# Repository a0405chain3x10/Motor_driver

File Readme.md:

# Discrete H-Bridge DC Motor Driver

This repository contains the KiCad schematics and PCB layout files for a custom DC motor driver. Designed around a discrete MOSFET H-Bridge topology, the board incorporates dedicated gate drivers and a hardware-level logic safety interlock to prevent catastrophic shoot-through conditions.

## Hardware Architecture
The motor driver is built to handle high-current DC loads using a robust discrete component approach:
*   **Power Delivery:** The main power stage accepts a 12V input via a dedicated screw terminal (J1), supported by a 220uF/25V electrolytic bulk capacitor (C7) to handle transient loads.
*   **Logic Power:** A separate 3.3V input (J3) is utilized to power the onboard logic gates and safely interface with low-voltage microcontrollers.
*   **H-Bridge Configuration:** The switching stage utilizes two PMOS (Q1, Q3) and two NMOS (Q2, Q4) transistors in a standard H-Bridge layout to control motor direction and speed.
*   **Gate Driving:** Two TC4428xOA ICs (U1, U2) are used to provide the necessary current to rapidly charge and discharge the MOSFET gates, ensuring highly efficient PWM switching and minimizing thermal dissipation.
*   **Motor Output:** The driven motor connects directly to the H-Bridge via a 2-pin screw terminal (J4) labeled `M+` and `M-`.

## Hardware Safety Interlock
To protect the H-Bridge from short circuits caused by simultaneous directional commands (shoot-through), the board features a physical logic-gate safety layer:
*   **Logic ICs:** The interlock circuit is constructed using standard DIP-packaged 74HC08 (AND) and 74HC04 (NOT/Inverter) logic chips.
*   **Signal Processing:** Raw `R` and `L` input signals from the control connector (J2) are processed through the logic gates to generate mutually exclusive `R_Safe` and `L_Safe` signals. 
*   **Fail-Safe Operation:** If both directional inputs are triggered simultaneously (either by software bug or electrical noise), the hardware logic overrides the input and prevents the active signals from reaching the TC4428xOA gate drivers, keeping the MOSFETs safely deactivated.

## PCB Layout & Design Features
The physical dual-layer board is optimized for current handling and thermal management:
*   **High-Current Routing:** The `M+` and `M-` motor output paths utilize exceptionally thick copper traces routed across both the top and bottom layers to handle heavy current loads without overheating.
*   **Thermal Management:** The four TO-220 MOSFETs (Q1-Q4) are aligned sequentially along the edge of the board, allowing them to share a single, continuous heatsink for optimal thermal dissipation.
*   **Mixed-Technology Assembly:** The design smartly combines through-hole components for robust mechanical connections (connectors, bulk capacitors, DIP logic ICs) with surface-mount (SMD) components for the gate drivers, decoupling capacitors, and pull-down resistors to save board space and optimize routing.

## Bill of Materials (BOM)

### Semiconductors & ICs
| Reference | Part | Package | Description | Quantity |
| :--- | :--- | :--- | :--- | :--- |
| U1, U2 | TC4428xOA | SOIC-8 (SMD) | 1.5A Dual High-Speed Gate Driver | 2 |
| Q1, Q3 | PMOS Transistor | TO-220 | High-Side P-Channel Power MOSFET | 2 |
| Q2, Q4 | NMOS Transistor | TO-220 | Low-Side N-Channel Power MOSFET | 2 |
| U5, U6 | 74HC08 | DIP-14 | Quad 2-Input AND Gate | 2 |
| U3, U4 | 74HC04 | DIP-14 | Hex Inverter (NOT Gate) | 2 |

### Passives (Resistors & Capacitors)
| Reference | Value | Package | Description | Quantity |
| :--- | :--- | :--- | :--- | :--- |
| C7 | 220uF / 25V | Radial (THT) | Bulk Electrolytic Decoupling Capacitor | 1 |
| C4, C6, C8 | 1uF / 25V | SMD | Ceramic Decoupling Capacitor | 3 |
| C3, C5, C9, C10, C11, C12, C13 | 100nF (0.1uF) | SMD | Ceramic Decoupling Capacitor | 7 |
| R1, R2, R3, R4 | 10 Ω | SMD | Gate Current Limiting Resistor | 4 |
| R5, R6, R7, R8 | 10k Ω | SMD | Input Signal Pull-down Resistor | 4 |
| R9, R10, R11, R12 | 47k Ω | SMD | Gate Pull-down Resistor | 4 |

### Connectors & Hardware
| Reference | Part | Description | Quantity |
| :--- | :--- | :--- | :--- |
| J1 | 2-Pin Screw Terminal | 12V Main Power Input | 1 |
| J4 | 2-Pin Screw Terminal | Motor Output (M+, M-) | 1 |
| J2 | 3-Pin Header/Terminal | Logic Inputs (R, L, GND) | 1 |
| J3 | 2-Pin Header/Terminal | 3.3V Logic Power Input | 1 |
| Heatsink | TO-220 Continuous | Multi-component heatsink across Q1-Q4 | 1 |

## Setup and Fabrication
1. Clone this repository to view or modify the design files in KiCad:
   ```bash
   git clone https://github.com/adityasoni0405/<your-repo-name>.git
   ```
2. Open `motor driver.kicad_pro` in KiCad to explore the schematic and PCB.
3. To fabricate the board, export the Gerber files directly from the `.kicad_pcb` layout interface. When ordering from a fabricator (e.g., JLCPCB, PCBWay), a standard 1.6mm thickness with 1oz copper is sufficient, but 2oz copper is recommended if driving high-current loads continuously.

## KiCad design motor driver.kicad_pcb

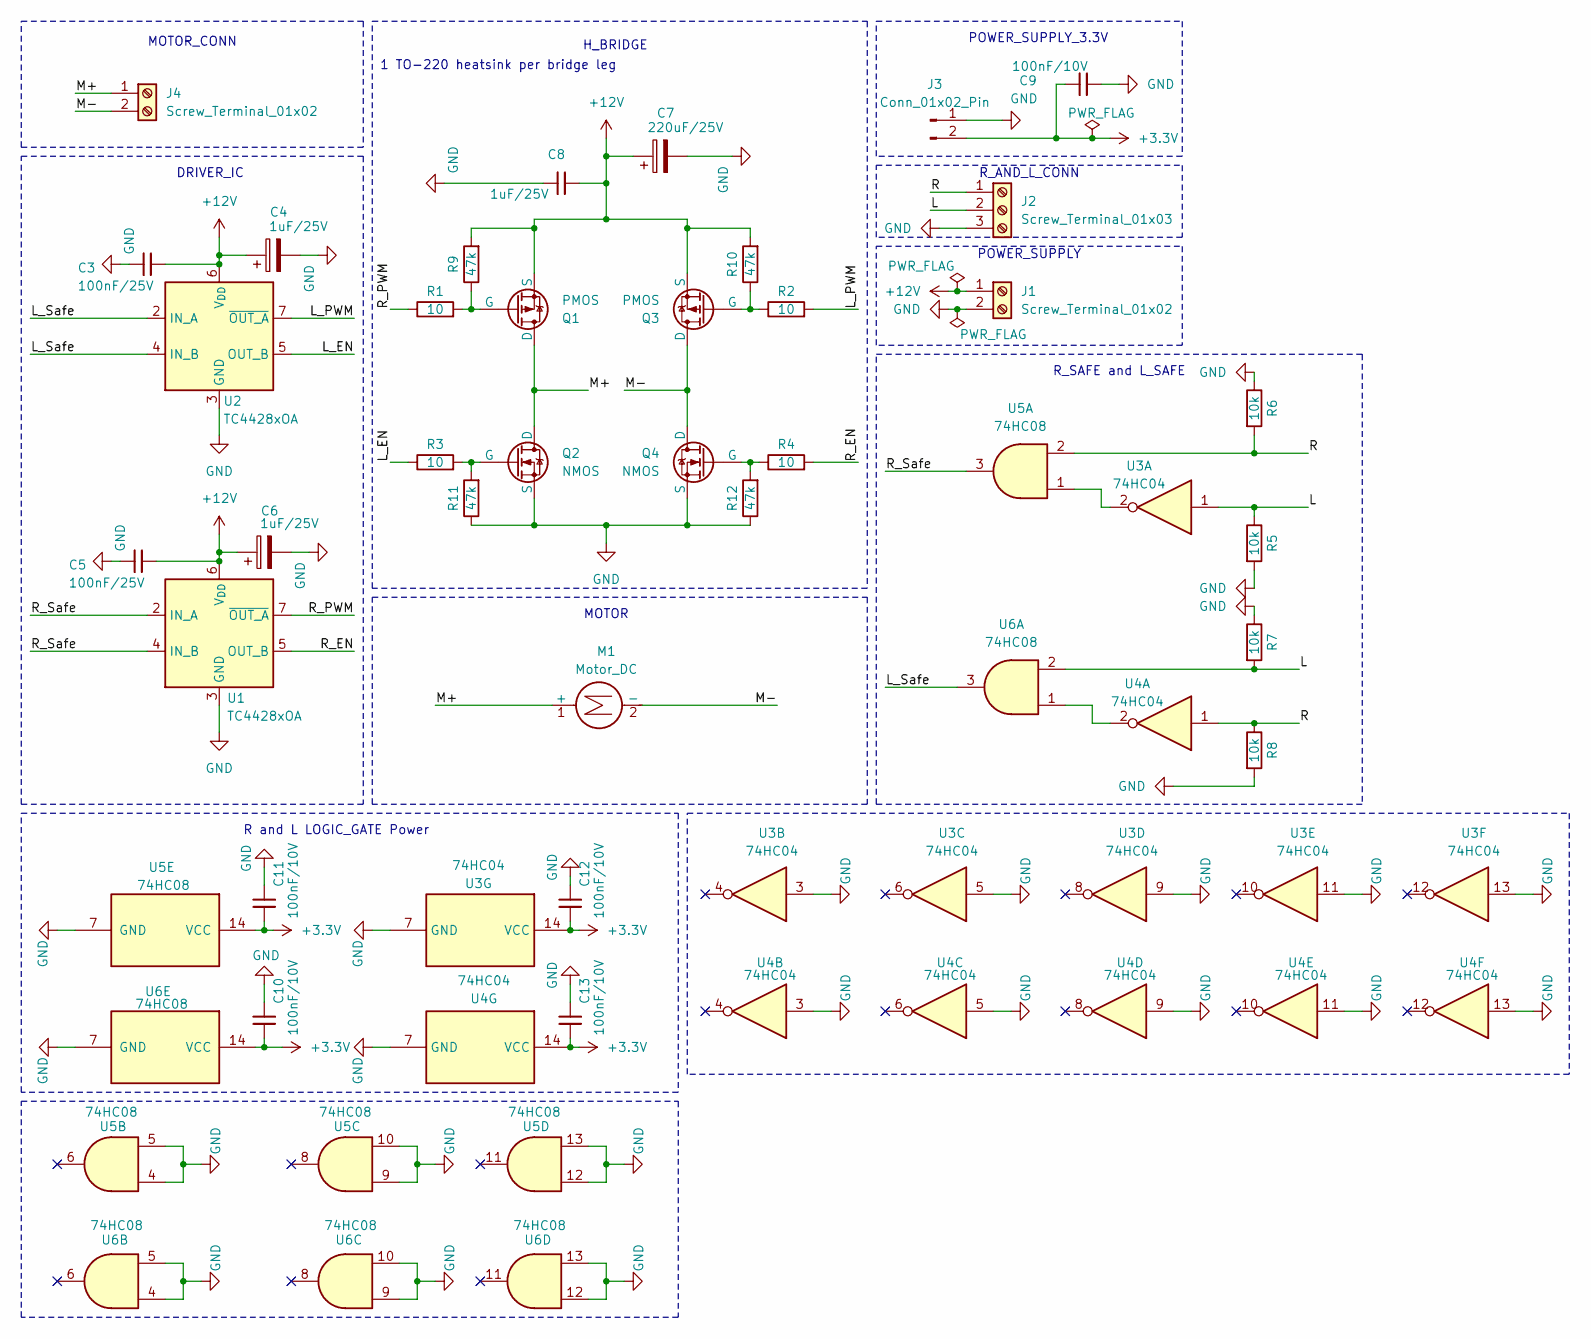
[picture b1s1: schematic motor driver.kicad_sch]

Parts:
C3, C5: 100nF/25V; C_0805_2012Metric
C4, C6, C8: 1uF/25V; C_0805_2012Metric
C7: 220uF/25V; CP_Elec_10x10.5
C9, C10, C11, C12, C13: 100nF/10V; C_0805_2012Metric
J1, J4: Screw_Terminal_01x02; TerminalBlock_Phoenix_MKDS-1,5-2-5.08_1x02_P5.08mm_Horizont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
J2: Screw_Terminal_01x03; PinHeader_1x03_P2.54mm_Vertical
J3: Conn_01x02_Pin; PinHeader_1x02_P2.54mm_Vertical
M1: Motor_DC; Maple_Mini
Q1, Q3: PMOS; TO-220-3_Vertical
Q2, Q4: NMOS; TO-220-3_Vertical
R1, R2, R3, R4: 10; R_0603_1608Metric
R5, R6, R7, R8: 10k; R_0603_1608Metric
R9, R10, R11, R12: 47k; R_0603_1608Metric
U1, U2: TC4428xOA; SOIC-8_3.9x4.9mm_P1.27mm
U3, U4: 74HC04; DIP-14_W7.62mm
U5, U6: 74HC08; DIP-14_W7.62mm

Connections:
+3.3V: C9.2, C10.1, C11.1, C12.1, C13.1, J3.2, U3.14 (VCC), U4.14 (VCC), U5.14 (VCC), U6.14 (VCC)
+12V: C3.1, C4.1, C5.1, C6.1, C7.1, C8.1, J1.1, Q1.3 (S), Q3.3 (S), R9.2, R10.2, U1.6 (V_{DD}), U2.6 (V_{DD})
/L: J2.2, R5.1, R7.2, U3.1, U6.2
/L_EN: R3.1, U2.5 (OUT_B)
/L_PWM: R2.2, U2.7 (~OUT_A)
/L_Safe: U2.2 (IN_A), U2.4 (IN_B), U6.3
/M+: J4.1, M1.1 (+), Q1.1 (D), Q2.1 (D)
/M-: J4.2, M1.2 (-), Q3.1 (D), Q4.1 (D)
/R: J2.1, R6.2, R8.1, U4.1, U5.2
/R_EN: R4.2, U1.5 (OUT_B)
/R_PWM: R1.1, U1.7 (~OUT_A)
/R_Safe: U1.2 (IN_A), U1.4 (IN_B), U5.3
GND: C3.2, C4.2, C5.2, C6.2, C7.2, C8.2, C9.1, C10.2, C11.2, C12.2, C13.2, J1.2, J2.3, J3.1, Q2.3 (S), Q4.3 (S), R5.2, R6.1, R7.1, R8.2, R11.1, R12.1, U1.3 (GND), U2.3 (GND), U3.3, U3.5, U3.7 (GND), U3.9, U3.11, U3.13, U4.3, U4.5, U4.7 (GND), U4.9, U4.11, U4.13, U5.4, U5.5, U5.7 (GND), U5.9, U5.10, U5.12, U5.13, U6.4, U6.5, U6.7 (GND), U6.9, U6.10, U6.12, U6.13
unnamed: Q1.2 (G), R1.2, R9.1
unnamed: Q2.2 (G), R3.2, R11.2
unnamed: Q3.2 (G), R2.1, R10.1
unnamed: Q4.2 (G), R4.1, R12.2
unnamed: U3.2, U5.1
unnamed: U4.2, U6.1

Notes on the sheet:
H_BRIDGE
R_AND_L_CONN
POWER_SUPPLY_3.3V
R_SAFE and L_SAFE
DRIVER_IC
1 TO-220 heatsink per bridge leg
MOTOR
MOTOR_CONN
R and L LOGIC_GATE Power
POWER_SUPPLY

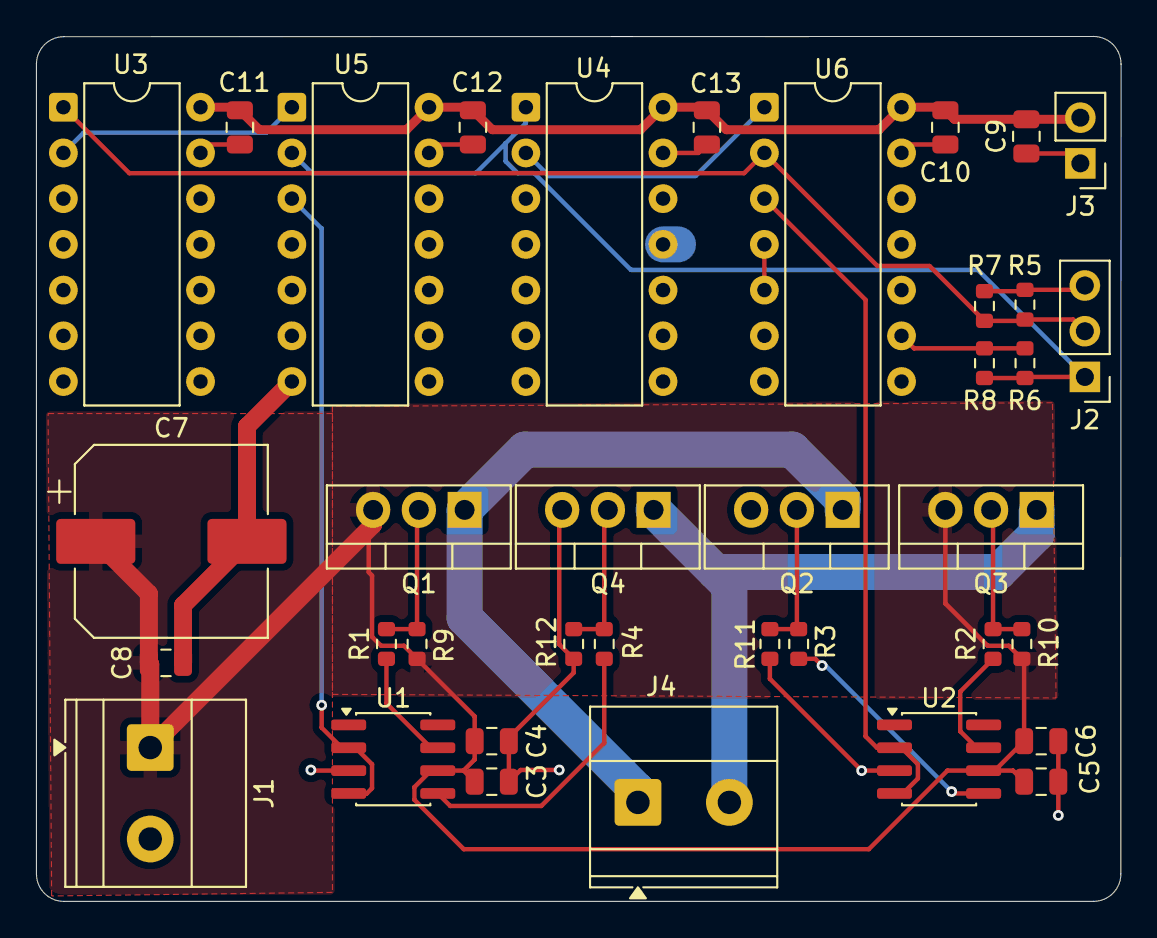
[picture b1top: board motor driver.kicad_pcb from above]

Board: 2 copper layers, 60.3 x 48.1 mm, 37 parts (0 on the bottom side), 19 nets.
